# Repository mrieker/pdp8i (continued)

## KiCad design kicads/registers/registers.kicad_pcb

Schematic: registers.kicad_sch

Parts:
J1, J2, J3, J4: Conn_02x20_Odd_Even; PinHeader_2x20_P2.54mm_Vertical
U1, U10, U19, U51: 74HC86; DIP-14_W7.62mm
U2, U3, U4, U5, U11, U12, U17, U18, U20, U21, U22, U26, U27, U52, U53, U54, U55, U56: 74LS153; DIP-16_W7.62mm
U6, U14, U23: 74LS283; DIP-16_W7.62mm
U7, U15, U24, U58, U85, U91, U117: 74LS08; DIP-14_W7.62mm
U8, U16, U25, U77: 74LS32; DIP-14_W7.62mm
U9, U62, U72, U73, U76, U78, U79, U82, U105, U113: 74LS10; DIP-14_W7.62mm
U13, U59, U63, U65, U66, U69, U74, U86, U97: 74LS00; DIP-14_W7.62mm
U28, U29, U30, U31, U32, U33: 74LS174; DIP-16_W7.62mm
U34, U35, U36: 74LS161; DIP-16_W7.62mm
U37, U38, U39, U40, U41, U42, U43, U44, U45, U46, U47, U48, U49: 74LS151; DIP-16_W7.62mm
U50, U104, U119, U120: 74HC74; DIP-14_W7.62mm
U57, U67, U90: 74LS04; DIP-14_W7.62mm
U60: 74LS02; DIP-14_W7.62mm
U61, U68, U70, U87, U89, U96: 74LS20; DIP-14_W7.62mm
U64, U75, U83, U88, U99: 74LS30; DIP-14_W7.62mm
U71, U106, U107, U108: 74LS11; DIP-14_W7.62mm
U80, U81, U110, U116, U118: 74HC00; DIP-14_W7.62mm
U84: 74LS175; DIP-16_W7.62mm
U92: 74HC138; DIP-16_W7.62mm
U93, U102, U109, U115: 74HC04; DIP-14_W7.62mm
U94, U98, U101, U112: 74LS27; DIP-14_W7.62mm
U95: 74LS21; DIP-14_W7.62mm
U100: 74HC02; DIP-14_W7.62mm
U103, U114: 74LS42; DIP-16_W7.62mm
U111: 74HC4075; DIP-14_W7.62mm

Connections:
/AA: U81.6, U101.3, U112.9
/ACCLEAR: J4.7, U118.5
/ACUM_0: J3.15, U1.1, U28.2 (Q0), U94.11
/ACUM_1: J3.7, U1.4, U28.5 (Q1), U94.10
/ACUM_2: J2.35, U1.9, U28.7 (Q2), U94.9
/ACUM_3: J2.27, U1.12, U28.10 (Q3), U98.11
/ACUM_4: J2.19, U10.1, U28.12 (Q4), U98.10
/ACUM_5: J2.12, U10.4, U28.15 (Q5), U98.9
/ACUM_6: J2.5, U10.9, U29.2 (Q0), U98.5
/ACUM_7: J1.34, U10.12, U29.5 (Q1), U98.4
/ACUM_8: J1.27, U19.1, U29.7 (Q2), U98.3
/ACUM_9: J1.19, U19.4, U29.10 (Q3), U98.13
/ACUM_10: J1.11, U19.9, U29.12 (Q4), U98.2
/ACUM_11: J1.3, U19.12, U29.15 (Q5), U86.12, U98.1
/BB: U77.1, U87.8, U101.4
/BRKRQST: J4.8
/BRKWRM: J4.9, U66.2, U79.11
/BUSINI: J4.22
/BWCOV: J4.23, U62.13, U104.5 (Q)
/CAINC: J4.10, U63.13, U72.13
/CC: U76.8, U77.2
/CC3: U67.4, U111.1, U118.9
/CLOK2: J4.3, U119.3 (C), U119.11 (C)
/CYCLE3: J4.11, U90.3
/DD: U22.2 (S1), U52.2 (S1), U53.2 (S1), U54.2 (S1), U55.2 (S1), U56.2 (S1), U81.8, U101.9
/DMADR_0: J3.18, U53.4 (I2a)
/DMADR_1: J3.10, U53.12 (I2b)
/DMADR_2: J2.38, U54.4 (I2a)
/DMADR_3: J2.30, U54.12 (I2b)
/DMADR_4: J2.22, U55.4 (I2a)
/DMADR_5: J2.15, U55.12 (I2b)
/DMADR_6: J2.8, U56.4 (I2a)
/DMADR_7: J1.37, U56.12 (I2b)
/DMADR_8: J1.30, U22.4 (I2a)
/DMADR_9: J1.22, U22.12 (I2b)
/DMADR_10: J1.14, U52.4 (I2a)
/DMADR_11: J1.6, U52.12 (I2b)
/DMADR_12: J3.25
/DMADR_13: J3.24
/DMADR_14: J3.23
/EE: U101.10, U105.8
/EXEFET: J4.24
/FF: U60.5, U96.8, U100.6, U101.11
/FLDSEL_0: J4.37
/FLDSEL_1: J4.38
/HH: U57.12, U112.1, U112.3
/HOLD: J4.12
/INBUS_0: J3.19, U53.5 (I1a)
/INBUS_1: J3.11, U53.11 (I1b)
/INBUS_2: J3.3, U54.5 (I1a)
/INBUS_3: J2.31, U54.11 (I1b)
/INBUS_4: J2.23, U55.5 (I1a)
/INBUS_5: J2.17, U55.11 (I1b)
/INBUS_6: J2.9, U56.5 (I1a)
/INBUS_7: J1.38, U56.11 (I1b)
/INBUS_8: J1.31, U22.5 (I1a), U84.4 (D0)
/INBUS_9: J1.23, U22.11 (I1b), U84.5 (D1)
/INBUS_10: J1.15, U52.5 (I1a), U84.12 (D2)
/INBUS_11: J1.7, U52.11 (I1b), U67.13
/INTAK: J4.25
/INTINH: J4.13
/INTRQST: J4.14
/IOP: J4.26, U63.4, U66.13, U109.3
/IOSKIP: J4.15, U62.5, U63.5
/IREG_8: U84.2 (Q0)
/IREG_9: J1.26, U84.7 (Q1), U92.1 (A0)
/IREG_10: J1.18, U84.10 (Q2), U92.2 (A1)
/IREG_11: J1.10, U84.14 (~Q3), U92.3 (A2)
/JJ: U60.6, U75.8, U100.5, U112.2, U112.4
/KK: U67.10, U112.10
/LINK: J4.27, U50.5 (Q), U51.5, U97.1
/LL: U89.6, U112.13
/LNKTOG: J4.16
/MADR_0: J3.16, U2.6 (I0a), U30.2 (Q0)
/MADR_1: J3.8, U2.10 (I0b), U30.5 (Q1)
/MADR_2: J2.36, U4.6 (I0a), U30.7 (Q2)
/MADR_3: J2.28, U4.10 (I0b), U30.10 (Q3), U95.5
/MADR_4: J2.20, U11.6 (I0a), U30.12 (Q4), U60.12
/MADR_5: J2.13, U11.10 (I0b), U30.15 (Q5), U60.11
/MADR_6: J2.6, U12.6 (I0a), U31.2 (Q0), U94.5
/MADR_7: J1.35, U12.10 (I0b), U31.5 (Q1), U91.13, U94.4
/MADR_8: J1.28, U20.6 (I0a), U31.7 (Q2), U91.10, U94.3
/MADR_9: J1.20, U20.10 (I0b), U31.10 (Q3), U91.5, U94.13
/MADR_10: J1.12, U21.6 (I0a), U31.12 (Q4), U91.2, U94.2
/MADR_11: J1.4, U21.10 (I0b), U31.15 (Q5), U58.13, U94.1
/MAJST_0: J4.20, U103.15 (A0)
/MAJST_1: J4.19, U103.14 (A1)
/MAJST_2: J4.18, U103.13 (A2)
/MAJST_3: J4.17, U57.11, U85.13, U103.12 (A3)
/MBUF_0: J3.17, U2.5 (I1a), U32.2 (Q0), U53.6 (I0a), U96.5, U101.13, U110.10
/MBUF_1: J3.9, U2.11 (I1b), U32.5 (Q1), U53.10 (I0b), U69.5
/MBUF_2: J2.37, U4.5 (I1a), U32.7 (Q2), U54.6 (I0a), U69.10, U77.5
/MBUF_3: J2.29, U4.11 (I1b), U32.10 (Q3), U51.10, U54.10 (I0b), U69.13
/MBUF_4: J2.21, U11.5 (I1a), U32.12 (Q4), U55.6 (I0a), U71.5, U97.2
/MBUF_5: J2.14, U11.11 (I1b), U32.15 (Q5), U55.10 (I0b), U71.9, U99.12
/MBUF_6: J2.7, U12.5 (I1a), U33.2 (Q0), U56.6 (I0a), U70.5, U86.13
/MBUF_7: J1.36, U33.5 (Q1), U56.10 (I0b), U58.12, U68.5, U91.1, U91.4, U91.9, U91.12, U118.10
/MBUF_8: J1.29, U22.6 (I0a), U33.7 (Q2), U60.9, U67.9, U96.4, U100.3
/MBUF_9: J1.21, U22.10 (I0b), U33.10 (Q3)
/MBUF_10: J1.13, U33.12 (Q4), U52.6 (I0a)
/MBUF_11: J1.5, U33.15 (Q5), U52.10 (I0b)
/MM: U73.12, U112.5
/MQUO_0: J3.20
/MQUO_1: J3.12
/MQUO_2: J3.4
/MQUO_3: J2.32
/MQUO_4: J2.24
/MQUO_5: J2.16
/MQUO_6: J2.10
/MQUO_7: J2.3
/MQUO_8: J1.32
/MQUO_9: J1.24
/MQUO_10: J1.16
/MQUO_11: J1.8
/NN: U109.2, U110.9, U112.11
/NXTMSBRK: J4.21
/NXTMS_0: J3.30, U114.15 (A0)
/NXTMS_1: J3.29, U114.14 (A1)
/NXTMS_2: J3.28, U114.13 (A2)
/NXTMS_3: J3.27, U114.12 (A3)
/PCTR_0: J3.21, U2.4 (I2a), U34.14 (Q0)
/PCTR_1: J3.13, U2.12 (I2b), U34.13 (Q1)
/PCTR_2: J3.5, U4.4 (I2a), U34.12 (Q2)
/PCTR_3: J2.33, U4.12 (I2b), U34.11 (Q3)
/PCTR_4: J2.25, U11.4 (I2a), U35.14 (Q0)
/PCTR_5: J2.18, U11.12 (I2b), U35.13 (Q1)
/PCTR_6: J2.11, U12.4 (I2a), U35.12 (Q2)
/PCTR_7: J2.4, U12.12 (I2b), U35.11 (Q3)
/PCTR_8: J1.33, U20.4 (I2a), U36.14 (Q0)
/PCTR_9: J1.25, U20.12 (I2b), U36.13 (Q1)
/PCTR_10: J1.17, U21.4 (I2a), U36.12 (Q2)
/PCTR_11: J1.9, U21.12 (I2b), U36.11 (Q3)
/PP: U81.11
/READSR: J3.26, U111.9
/RESET: J4.4
/RUN: J4.28, U58.1
/SCTR_0: J3.22
/SCTR_1: J3.14
/SCTR_2: J3.6
/SCTR_3: J2.34
/SCTR_4: J2.26
/TP1: J4.33, U57.3, U85.1, U86.1
/TP2: J4.34, U13.4, U63.9, U68.1, U70.1, U117.4
/TP3: J4.35, U57.1, U58.4, U58.9
/TP4: J4.36, U116.4
/TS1: J4.29, U109.11
/TS2: J4.30, U13.12, U72.1, U73.3, U74.1, U78.1, U78.3, U79.1, U79.9, U80.9, U97.9, U117.10
/TS3: J4.31, U9.3, U13.1, U13.9, U66.12, U71.1, U71.3, U72.3, U72.9, U73.9, U74.9, U78.9, U79.3, U80.1, U82.1, U105.3
/TS4: J4.32, U70.9, U74.4, U74.12, U76.1, U76.3, U80.4, U80.12, U81.1, U86.9, U105.1
/_AA1: U81.4, U82.12
/_AA2: U81.5, U86.8
/_BB1: U87.9, U90.2
/_BB2: U87.10, U109.10
/_BB3: U79.8, U87.12
/_BB4: U74.3, U87.13
/_CC1: U66.11, U76.9, U118.12
/_CC2: U74.8, U76.10, U118.13
/_CC3: U9.6, U67.3, U76.11, U77.4
/_DD1: U74.6, U81.9
/_DD2: U76.12, U81.10
/_EE1: U72.6, U105.9
/_EE2: U76.6, U105.10
/_EE3: U74.11, U105.11
/_FF1: U78.12, U96.9
/_FF2: U78.6, U96.10
/_FF3: U96.12, U97.8
/_FF4: U72.12, U96.13
/_HH1: U57.13, U60.1
/_JJ1: U75.4, U86.6
/_JJ2: U75.5, U97.11
/_JJ3: U75.6, U79.6
/_JJ4: U75.11, U80.3
/_JJ5: U75.12, U80.6
/_KK1: U67.11, U73.6
/_LL1: U79.12, U89.1
/_LL2: U80.8, U89.2
/_LL3: U80.11, U89.4
/_LL4: U89.5, U105.12
/_MM1: U73.1, U78.8
/_MM2: U73.2, U81.3
/_MM3: U70.8, U73.13
/_NN1: U72.8, U109.1, U113.4
/_PP1: U73.8, U81.12, U109.5
/_PP2: U81.13, U105.6, U113.3
/_acres: U28.1 (~Mr), U29.1 (~Mr), U68.6
/_asel_0: U2.14 (S0), U4.14 (S0), U11.14 (S0), U12.14 (S0), U20.14 (S0), U21.14 (S0), U87.4, U112.12
/_asel_1: U2.2 (S1), U4.2 (S1), U11.2 (S1), U12.2 (S1), U20.2 (S1), U21.2 (S1), U87.5, U112.6
/_irand: U82.9, U92.15 (~Y0), U93.13
/_irdca: U82.11, U92.12 (~Y3), U93.5, U113.10
/_iriot: U92.9 (~Y6)
/_irisz: U92.13 (~Y2), U93.9, U113.9
/_irjmp: U60.8, U92.10 (~Y5), U93.1
/_irjms: U92.11 (~Y4), U93.3, U113.11
/_iropr: U67.5, U70.13, U92.7 (~Y7), U100.2, U101.1
/_irtad: U82.10, U92.14 (~Y1), U93.11
/_ldadclk: U9.1, U116.12, U119.8 (~Q)
/_lnres: U50.1 (~R), U70.6
/_msdepos: U64.12, U102.11, U103.10 (8)
/_msexec: U90.13, U103.4 (3), U116.1
/_msintak: U64.11, U89.13, U102.9, U103.9 (7)
/_mswrdct: U64.4, U102.1, U103.5 (4), U116.2
/_pcld: U34.9 (~PE), U35.9 (~PE), U36.9 (~PE), U58.3
/acclk: U28.9 (Cp), U29.9 (Cp), U58.8
/acxx_0: U1.3, U2.3 (I3a)
/acxx_1: U1.6, U2.13 (I3b)
/acxx_2: U1.8, U4.3 (I3a)
/acxx_3: U1.11, U4.13 (I3b)
/acxx_4: U10.3, U11.3 (I3a)
/acxx_5: U10.6, U11.13 (I3b)
/acxx_6: U10.8, U12.3 (I3a)
/acxx_7: U10.11, U12.13 (I3b)
/acxx_8: U19.3, U20.3 (I3a)
/acxx_9: U19.6, U20.13 (I3b)
/acxx_10: U19.8, U21.3 (I3a)
/acxx_11: U19.11, U21.13 (I3b)
/alua_0: U2.7 (Za), U6.5 (A1), U7.1, U8.1
/alua_1: U2.9 (Zb), U6.3 (A2), U7.4, U8.4
/alua_2: U4.7 (Za), U6.14 (A3), U7.9, U8.9
/alua_3: U4.9 (Zb), U6.12 (A4), U7.12, U8.12
/alua_4: U11.7 (Za), U14.5 (A1), U15.1, U16.1
/alua_5: U11.9 (Zb), U14.3 (A2), U15.4, U16.4
/alua_6: U12.7 (Za), U14.14 (A3), U15.9, U16.9
/alua_7: U12.9 (Zb), U14.12 (A4), U15.12, U16.12
/alua_8: U20.7 (Za), U23.5 (A1), U24.1, U25.1
/alua_9: U20.9 (Zb), U23.3 (A2), U24.4, U25.4
/alua_10: U21.7 (Za), U23.14 (A3), U24.9, U25.9
/alua_11: U21.9 (Zb), U23.12 (A4), U24.12, U25.12
/alub_0: U6.6 (B1), U7.2, U8.2, U53.7 (Za)
/alub_1: U6.2 (B2), U7.5, U8.5, U53.9 (Zb)
/alub_2: U6.15 (B3), U7.10, U8.10, U54.7 (Za)
/alub_3: U6.11 (B4), U7.13, U8.13, U54.9 (Zb)
/alub_4: U14.6 (B1), U15.2, U16.2, U55.7 (Za)
/alub_5: U14.2 (B2), U15.5, U16.5, U55.9 (Zb)
/alub_6: U14.15 (B3), U15.10, U16.10, U56.7 (Za)
/alub_7: U14.11 (B4), U15.13, U16.13, U56.9 (Zb)
/alub_8: U22.7 (Za), U23.6 (B1), U24.2, U25.2
/alub_9: U22.9 (Zb), U23.2 (B2), U24.5, U25.5
/alub_10: U23.15 (B3), U24.10, U25.10, U52.7 (Za)
/alub_11: U23.11 (B4), U24.13, U25.13, U52.9 (Zb)
/aluq_0: U3.7 (Za), U30.3 (D0), U32.3 (D0), U34.3 (D0), U37.12 (I7), U38.14 (I5), U39.15 (I4), U43.13 (I6), U48.2 (I2), U49.1 (I3)
/aluq_1: U3.9 (Zb), U30.4 (D1), U32.4 (D1), U34.4 (D1), U37.1 (I3), U38.12 (I7), U39.14 (I5), U40.15 (I4), U44.13 (I6), U49.2 (I2)
/aluq_2: U5.7 (Za), U30.6 (D2), U32.6 (D2), U34.5 (D2), U37.2 (I2), U38.1 (I3), U39.12 (I7), U40.14 (I5), U41.15 (I4), U45.13 (I6)
/aluq_3: U5.9 (Zb), U30.11 (D3), U32.11 (D3), U34.6 (D3), U38.2 (I2), U39.1 (I3), U40.12 (I7), U41.14 (I5), U42.15 (I4), U46.13 (I6)
/aluq_4: U17.7 (Za), U30.13 (D4), U32.13 (D4), U35.3 (D0), U39.2 (I2), U40.1 (I3), U41.12 (I7), U42.14 (I5), U43.15 (I4), U47.13 (I6)
/aluq_5: U17.9 (Zb), U30.14 (D5), U32.14 (D5), U35.4 (D1), U40.2 (I2), U41.1 (I3), U42.12 (I7), U43.14 (I5), U44.15 (I4), U48.13 (I6)
/aluq_6: U18.7 (Za), U31.3 (D0), U33.3 (D0), U35.5 (D2), U37.13 (I6), U41.2 (I2), U42.1 (I3), U43.12 (I7), U44.14 (I5), U45.15 (I4)
/aluq_7: U18.9 (Zb), U31.4 (D1), U33.4 (D1), U35.6 (D3), U38.13 (I6), U42.2 (I2), U43.1 (I3), U44.12 (I7), U45.14 (I5), U46.15 (I4)
/aluq_8: U26.7 (Za), U31.6 (D2), U33.6 (D2), U36.3 (D0), U39.13 (I6), U43.2 (I2), U44.1 (I3), U45.12 (I7), U46.14 (I5), U47.15 (I4)
/aluq_9: U26.9 (Zb), U31.11 (D3), U33.11 (D3), U36.4 (D1), U40.13 (I6), U44.2 (I2), U45.1 (I3), U46.12 (I7), U47.14 (I5), U48.15 (I4)
/aluq_10: U27.7 (Za), U31.13 (D4), U33.13 (D4), U36.5 (D2), U41.13 (I6), U45.2 (I2), U46.1 (I3), U47.12 (I7), U48.14 (I5), U49.15 (I4)
/aluq_11: U27.9 (Zb), U31.14 (D5), U33.14 (D5), U36.6 (D3), U37.15 (I4), U42.13 (I6), U46.2 (I2), U47.1 (I3), U48.12 (I7), U49.14 (I5)
/aluq_12: U37.14 (I5), U38.15 (I4), U47.2 (I2), U48.1 (I3), U49.12 (I7), U49.13 (I6), U51.3
/autoinc: U65.5, U78.13, U95.6
/azero: U2.1 (Ea), U2.15 (Eb), U4.1 (Ea), U4.15 (Eb), U11.1 (Ea), U11.15 (Eb), U12.1 (Ea), U12.15 (Eb), U20.1 (Ea), U20.15 (Eb), U21.1 (Ea), U21.15 (Eb), U110.3
/bsel_0: U22.14 (S0), U52.14 (S0), U53.14 (S0), U54.14 (S0), U55.14 (S0), U56.14 (S0), U77.3
/bzero: U22.1 (Ea), U22.15 (Eb), U52.1 (Ea), U52.15 (Eb), U53.1 (Ea), U53.15 (Eb), U54.1 (Ea), U54.15 (Eb), U55.1 (Ea), U55.15 (Eb), U56.1 (Ea), U56.15 (Eb), U87.6
/cclears: U101.5, U118.3
/cin: U6.7 (C0), U110.6
/comac: U1.2, U1.5, U1.10, U1.13, U10.2, U10.5, U10.10, U10.13, U19.2, U19.5, U19.10, U19.13, U71.8
/comln: U51.4, U71.6
/cout: U23.9 (C4), U51.1, U104.2 (D)
/dirjmp: U59.5, U60.10, U78.11
/efaddr_7: U12.11 (I1b), U91.11
/efaddr_8: U20.5 (I1a), U91.8
/efaddr_9: U20.11 (I1b), U91.6
/efaddr_10: U21.5 (I1a), U91.3
/efaddr_11: U21.11 (I1b), U58.11
/extarithexec: U74.10, U109.13, U110.11
/g2skip: U9.11, U51.8
/group1: U68.4, U70.4, U71.2, U71.4, U71.10, U72.11, U77.12, U100.1, U116.10
/group2: U9.5, U9.10, U77.13, U101.12
/irand: U73.11, U93.12
/irandtaddca: U66.10, U82.8
/irdca: U73.5, U82.13, U93.6
/irisz: U62.2, U78.5, U93.8
/irjmp: U59.2, U72.5, U93.2
/irjms: U59.10, U79.5, U79.13, U93.4
/iropr: U62.4, U67.6, U96.1, U97.4, U105.13
/irtad: U69.2, U93.10, U105.5
/lnclk: U50.3 (C), U58.6
/maload: U30.9 (Cp), U31.9 (Cp), U116.11
/mbload: U32.9 (Cp), U33.9 (Cp), U63.3
/msbreak: U66.1, U79.10, U102.6
/mscurad: U63.12, U72.2, U74.13, U102.4
/msdefer: U59.1, U65.4, U72.4, U76.5, U78.2, U90.10
/msdepos: U65.13, U74.2, U97.13, U102.10, U117.9
/msexam: U65.10, U86.5, U102.12
/msexec: U59.9, U62.1, U62.3, U65.1, U66.9, U69.1, U73.4, U73.10, U78.4, U79.2, U79.4, U82.2, U90.12, U97.5, U105.4
/msfetch: U9.4, U9.9, U13.5, U13.13, U59.4, U66.4, U68.2, U70.2, U70.12, U71.11, U71.13, U72.10, U78.10, U85.2, U90.8, U96.2, U116.9
/msintak: U80.2, U80.10, U86.2, U102.8
/mspwron: U90.6
/mswrdct: U80.5, U97.10, U102.2
/nxtmsbreak: U76.2, U115.12
/nxtmsdefer: U81.2, U115.6
/nxtmsexec: U70.10, U76.4, U105.2, U115.8
/nxtmsfetch: U80.13, U115.4
/nxtmsintak: U86.10, U109.8
/nxtmspwron: U115.2
/nxtmswrdct: U74.5, U115.10
/pcclk: U9.12, U34.2 (CP), U35.2 (CP), U36.2 (CP)
/pcinc: U34.7 (CEP), U34.10 (CET), U35.7 (CEP), U36.7 (CEP), U59.11
/qsel_0: U3.14 (S0), U5.14 (S0), U17.14 (S0), U18.14 (S0), U26.14 (S0), U27.14 (S0), U109.6
/qsel_1: U3.2 (S1), U5.2 (S1), U17.2 (S1), U18.2 (S1), U26.2 (S1), U27.2 (S1), U113.6
/qsum_0: U3.4 (I2a), U6.4 (S1)
/qsum_1: U3.12 (I2b), U6.1 (S2)
/qsum_2: U5.4 (I2a), U6.13 (S3)
/qsum_3: U5.12 (I2b), U6.10 (S4)
/rotq_0: U28.3 (D0), U37.5 (Z)
/rotq_1: U28.4 (D1), U38.5 (Z)
/rotq_2: U28.6 (D2), U39.5 (Z)
/rotq_3: U28.11 (D3), U40.5 (Z)
/rotq_4: U28.13 (D4), U41.5 (Z)
/rotq_5: U28.14 (D5), U42.5 (Z)
/rotq_6: U29.3 (D0), U43.5 (Z)
/rotq_7: U29.4 (D1), U44.5 (Z)
/rotq_8: U29.6 (D2), U45.5 (Z)
/rotq_9: U29.11 (D3), U46.5 (Z)
/rotq_10: U29.13 (D4), U47.5 (Z)
/rotq_11: U29.14 (D5), U48.5 (Z)
/rotq_12: U49.5 (Z), U50.2 (D)
/swCONT: J3.35, U85.12
/swDEPOS: J3.34, U65.12, U97.12
/swEXAM: J3.33, U65.9, U86.4
/swLDAD: J3.32, U57.9, U90.1, U111.2
/swSINST: J3.38
/swSSTEP: J3.37
/swSTART: J3.36, U60.2
/swSTOP: J3.31
GND: J1.39, J1.40, J2.39, J2.40, J3.39, J3.40, J4.39, J4.40, U2.8 (GND), U3.1 (Ea), U3.3 (I3a), U3.8 (GND), U3.13 (I3b), U3.15 (Eb), U4.8 (GND), U5.1 (Ea), U5.3 (I3a), U5.8 (GND), U5.13 (I3b), U5.15 (Eb), U6.8 (GND), U11.8 (GND), U12.8 (GND), U14.8 (GND), U17.1 (Ea), U17.3 (I3a), U17.8 (GND), U17.13 (I3b), U17.15 (Eb), U18.1 (Ea), U18.3 (I3a), U18.8 (GND), U18.13 (I3b), U18.15 (Eb), U20.8 (GND), U21.8 (GND), U22.8 (GND), U23.8 (GND), U26.1 (Ea), U26.3 (I3a), U26.8 (GND), U26.13 (I3b), U26.15 (Eb), U27.1 (Ea), U27.3 (I3a), U27.8 (GND), U27.13 (I3b), U27.15 (Eb), U28.8 (GND), U29.8 (GND), U30.8 (GND), U31.8 (GND), U32.8 (GND), U33.8 (GND), U34.8 (GND), U35.8 (GND), U36.8 (GND), U37.3 (I1), U37.4 (I0), U37.7 (~E), U37.8 (GND), U38.3 (I1), U38.4 (I0), U38.7 (~E), U38.8 (GND), U39.3 (I1), U39.4 (I0), U39.7 (~E), U39.8 (GND), U40.3 (I1), U40.4 (I0), U40.7 (~E), U40.8 (GND), U41.3 (I1), U41.4 (I0), U41.7 (~E), U41.8 (GND), U42.3 (I1), U42.4 (I0), U42.7 (~E), U42.8 (GND), U43.3 (I1), U43.4 (I0), U43.7 (~E), U43.8 (GND), U44.3 (I1), U44.4 (I0), U44.7 (~E), U44.8 (GND), U45.3 (I1), U45.4 (I0), U45.7 (~E), U45.8 (GND), U46.3 (I1), U46.4 (I0), U46.7 (~E), U46.8 (GND), U47.3 (I1), U47.4 (I0), U47.7 (~E), U47.8 (GND), U48.3 (I1), U48.4 (I0), U48.7 (~E), U48.8 (GND), U49.3 (I1), U49.4 (I0), U49.7 (~E), U49.8 (GND), U52.8 (GND), U53.8 (GND), U54.8 (GND), U55.8 (GND), U56.8 (GND), U84.8 (GND), U92.4 (~E0), U92.5 (~E1), U92.8 (GND), U103.8 (GND), U114.8 (GND)
unnamed: U3.6 (I0a), U8.3
unnamed: U3.10 (I0b), U8.6
unnamed: U3.5 (I1a), U7.3
unnamed: U3.11 (I1b), U7.6
unnamed: U5.6 (I0a), U8.8
unnamed: U5.10 (I0b), U8.11
unnamed: U5.5 (I1a), U7.8
unnamed: U5.11 (I1b), U7.11
unnamed: U13.2, U61.6
unnamed: U13.3, U59.13
unnamed: U9.2, U13.6
unnamed: U13.8, U58.2
unnamed: U13.10, U89.8
unnamed: U13.11, U59.12
unnamed: U6.9 (C4), U14.7 (C0)
unnamed: U14.9 (C4), U23.7 (C0)
unnamed: U14.4 (S1), U17.4 (I2a)
unnamed: U14.1 (S2), U17.12 (I2b)
unnamed: U14.13 (S3), U18.4 (I2a)
unnamed: U14.10 (S4), U18.12 (I2b)
unnamed: U16.3, U17.6 (I0a)
unnamed: U16.6, U17.10 (I0b)
unnamed: U15.3, U17.5 (I1a)
unnamed: U15.6, U17.11 (I1b)
unnamed: U16.8, U18.6 (I0a)
unnamed: U16.11, U18.10 (I0b)
unnamed: U15.8, U18.5 (I1a)
unnamed: U15.11, U18.11 (I1b)
unnamed: U23.4 (S1), U26.4 (I2a)
unnamed: U23.1 (S2), U26.12 (I2b)
unnamed: U23.13 (S3), U27.4 (I2a)
unnamed: U23.10 (S4), U27.12 (I2b)
unnamed: U25.3, U26.6 (I0a)
unnamed: U25.6, U26.10 (I0b)
unnamed: U24.3, U26.5 (I1a)
unnamed: U24.6, U26.11 (I1b)
unnamed: U25.8, U27.6 (I0a)
unnamed: U25.11, U27.10 (I0b)
unnamed: U24.8, U27.5 (I1a)
unnamed: U24.11, U27.11 (I1b)
unnamed: U34.15 (TC), U35.10 (CET)
unnamed: U35.15 (TC), U36.10 (CET)
unnamed: U37.11 (S0), U38.11 (S0), U39.11 (S0), U40.11 (S0), U41.11 (S0), U42.11 (S0), U43.11 (S0), U44.11 (S0), U45.11 (S0), U46.11 (S0), U47.11 (S0), U48.11 (S0), U49.11 (S0), U69.6
unnamed: U37.10 (S1), U38.10 (S1), U39.10 (S1), U40.10 (S1), U41.10 (S1), U42.10 (S1), U43.10 (S1), U44.10 (S1), U45.10 (S1), U46.10 (S1), U47.10 (S1), U48.10 (S1), U49.10 (S1), U69.8
unnamed: U37.9 (S2), U38.9 (S2), U39.9 (S2), U40.9 (S2), U41.9 (S2), U42.9 (S2), U43.9 (S2), U44.9 (S2), U45.9 (S2), U46.9 (S2), U47.9 (S2), U48.9 (S2), U49.9 (S2), U69.11
unnamed: U51.2, U51.6
unnamed: U51.9, U82.6
unnamed: U9.13, U57.2
unnamed: U57.4, U63.1
unnamed: U58.5, U62.8
unnamed: U58.10, U68.8
unnamed: U59.3, U89.10
unnamed: U59.6, U89.9
unnamed: U59.8, U89.12
unnamed: U60.3, U85.11
unnamed: U60.13, U95.4
unnamed: U9.8, U61.1
unnamed: U61.2, U62.12
unnamed: U61.4, U62.6
unnamed: U61.5, U63.6
unnamed: U62.11, U69.3
unnamed: U63.2, U63.8
unnamed: U63.10, U64.8
unnamed: U63.11, U64.5
unnamed: U64.2, U65.6
unnamed: U64.3, U65.3
unnamed: U64.6, U66.3
unnamed: U66.5, U77.11
unnamed: U66.6, U68.12
unnamed: U66.8, U68.10
unnamed: U69.4, U69.9, U69.12, U71.12
unnamed: U76.13, U90.4
unnamed: U77.6, U87.1
unnamed: U82.3, U86.11
unnamed: U82.4, U99.8
unnamed: U82.5, U97.3
unnamed: U84.9 (Cp), U85.3
unnamed: U67.12, U84.13 (D3)
unnamed: U84.1 (~Mr), U86.3
unnamed: U94.6, U95.2
unnamed: U94.8, U99.11
unnamed: U94.12, U95.1
unnamed: U98.6, U99.4, U99.5
unnamed: U98.8, U99.6
unnamed: U98.12, U99.1, U99.2, U99.3
unnamed: U100.4, U113.5
unnamed: U67.8, U101.2
unnamed: U101.6, U110.1
unnamed: U101.8, U110.2
unnamed: U90.5, U103.1 (0)
unnamed: U90.9, U103.2 (1)
unnamed: U90.11, U103.3 (2)
unnamed: U102.3, U103.6 (5)
unnamed: U102.5, U103.7 (6)
unnamed: U102.13, U103.11 (9)
unnamed: U104.3 (C), U117.6
unnamed: U68.9, U109.4
unnamed: U62.9, U68.13, U109.12
unnamed: U60.4, U110.4
unnamed: U110.5, U110.8
unnamed: U96.6, U110.12
unnamed: U97.6, U110.13
unnamed: U111.8, U117.8
unnamed: U87.2, U112.8
unnamed: U57.8, U113.1
unnamed: U65.8, U113.2
unnamed: U65.2, U113.8
unnamed: U65.11, U113.13
unnamed: U114.1 (0), U115.1
unnamed: U114.2 (1), U115.3
unnamed: U114.3 (2), U115.5
unnamed: U114.4 (3), U115.9
unnamed: U114.5 (4), U115.11
unnamed: U114.7 (6), U115.13
unnamed: U109.9, U114.9 (7)
unnamed: U116.3, U117.5
unnamed: U57.10, U116.5
unnamed: U62.10, U116.8
unnamed: U116.6, U116.13
unnamed: U118.1, U118.6
unnamed: U118.2, U118.8
unnamed: U118.4, U118.11
unnamed: U119.5 (Q), U119.12 (D)
unnamed: U113.12, U119.1 (~R), U119.13 (~R)
VCC: J1.1, J1.2, J2.1, J2.2, J3.1, J3.2, J4.1, J4.2, U2.16 (VCC), U3.16 (VCC), U4.16 (VCC), U5.16 (VCC), U6.16 (VCC), U11.16 (VCC), U12.16 (VCC), U14.16 (VCC), U17.16 (VCC), U18.16 (VCC), U20.16 (VCC), U21.16 (VCC), U22.16 (VCC), U23.16 (VCC), U26.16 (VCC), U27.16 (VCC), U28.16 (VCC), U29.16 (VCC), U30.1 (~Mr), U30.16 (VCC), U31.1 (~Mr), U31.16 (VCC), U32.1 (~Mr), U32.16 (VCC), U33.1 (~Mr), U33.16 (VCC), U34.1 (~MR), U34.16 (VCC), U35.1 (~MR), U35.16 (VCC), U36.1 (~MR), U36.16 (VCC), U37.16 (VCC), U38.16 (VCC), U39.16 (VCC), U40.16 (VCC), U41.16 (VCC), U42.16 (VCC), U43.16 (VCC), U44.16 (VCC), U45.16 (VCC), U46.16 (VCC), U47.16 (VCC), U48.16 (VCC), U49.16 (VCC), U50.4 (~S), U52.16 (VCC), U53.16 (VCC), U54.16 (VCC), U55.16 (VCC), U56.16 (VCC), U64.1, U75.1, U75.2, U75.3, U84.16 (VCC), U92.6 (E2), U92.16 (VCC), U103.16 (VCC), U104.1 (~R), U104.4 (~S), U114.16 (VCC), U119.2 (D), U119.4 (~S), U119.10 (~S)

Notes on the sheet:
TS3: MADR <= MADR + 1
TS4: MADR <= MBUF
TS2: MBUF <= MBUF + 1
TS2: MBUF <= PCTR
load MADR after a 2 cycle delay after LDAD,EXAM,DEPOS
TS3: ACUM <= ACUM + MBUF_0
clock in new MADR except EXAM and DEPOS cycles
swLDAD: MADR <= INBUS (swREG)
TS4: MADR <= efaddr
TS3: ACUM <= ACUM | INBUS (group2)
TS3: ACUM <= 0
TS4: MADR <= 0
LSB
AA: ? <= 0 : A=ZERO, B=ZERO, OR BB: ? <= INBUS : A=ZERO, B=INBUS, OR CC: ? <= ACUM | INBUS : A=ACUM, B=INBUS, OR DD: ? <= DMADR : A=ZERO, B=DMADR, OR EE: ? <= MBUF : A=ZERO, B=MBUF, OR FF: ? <= MBUF + 1 : A=ZERO, B=MBUF, ADD, CIN=1 HH: ? <= MADR : A=MADR, B=ZERO, OR JJ: ? <= MADR + 1 : A=MADR, B=ZE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
TS2: MBUF <= ACUM
contx | swSTART: PCTR <= MADR
INBUS ----- TS1: data from memory TS2 & BREAK & BRKWRM: dma data from i/o dev IOP: pio data from i/o device
TS3: ACUM <= ACUM + MBUF
TS3: PCTR <= efaddr
TS3: PCTR <= MADR + 1
AZERO = AA | BB | CC1 & ACCLR | CC2 & ACCLR | CC3 & G2CLA | DD | EE | FF ASEL_0 (PCTR,MADR) = HH | JJ | LL ASEL_1 (efad,MADR) = HH | JJ | MM BZERO = AA | CC3 & ~G2OSR | HH | JJ | KK | LL | MM | NN BSEL_0 (INBUS) = BB | CC BSEL_1 (DMADR) = DD CIN = FF | JJ | NN & MBUF_0 QSEL_0 (AND) = PP1 QSEL_1 (AD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
TS2: MBUF <= INBUS (swREG)
asserted (low) when doing Group2 CLA
MSB
TS4: MADR <= PCTR
TS4: MADR <= DMADR
gate SWREG onto INBUS * during TS3 of Group2 for OSR * while LDAD held down to load MADR * during TS2 while doing deposit
complement ACUM value * must have Group1 instr * must have CMA bit * must be doing FETCH cycle
Clear ACUM for Group1 CLA at TP2
TS2: MBUF <= INBUS (dma data)
TS3: ACUM <= ACUM | INBUS (io data)
asserted (high) to force zero in alua during TS3
TS1: MBUF <= INBUS (mem data)
swEXAM: MADR <= MADR + 1
save overflow bit at TP2 * EXEC: used for ISZ skip must be valid until same TP3 * WRDCT: used for BWCOV must be valid until BREAK TP3
swDEPOS: MADR <= MADR + 1
current cycle is performing extended arithmetic accumulator and link get clocked at TP3 in these cycles FETCH: must have opcode 111 1xx xxx xx1 EXEC: must have opcode 111 xxx xxx xxx it is only OPR opcode that uses EXEC state
low when doing Group2 with OSR bit low blocking SR coming in on INBUS
asserted (low) when ACCLEAR is asserted (high) and doing IOT or ext arith
TS3: ACUM <= ACUM | INBUS (ext arith)

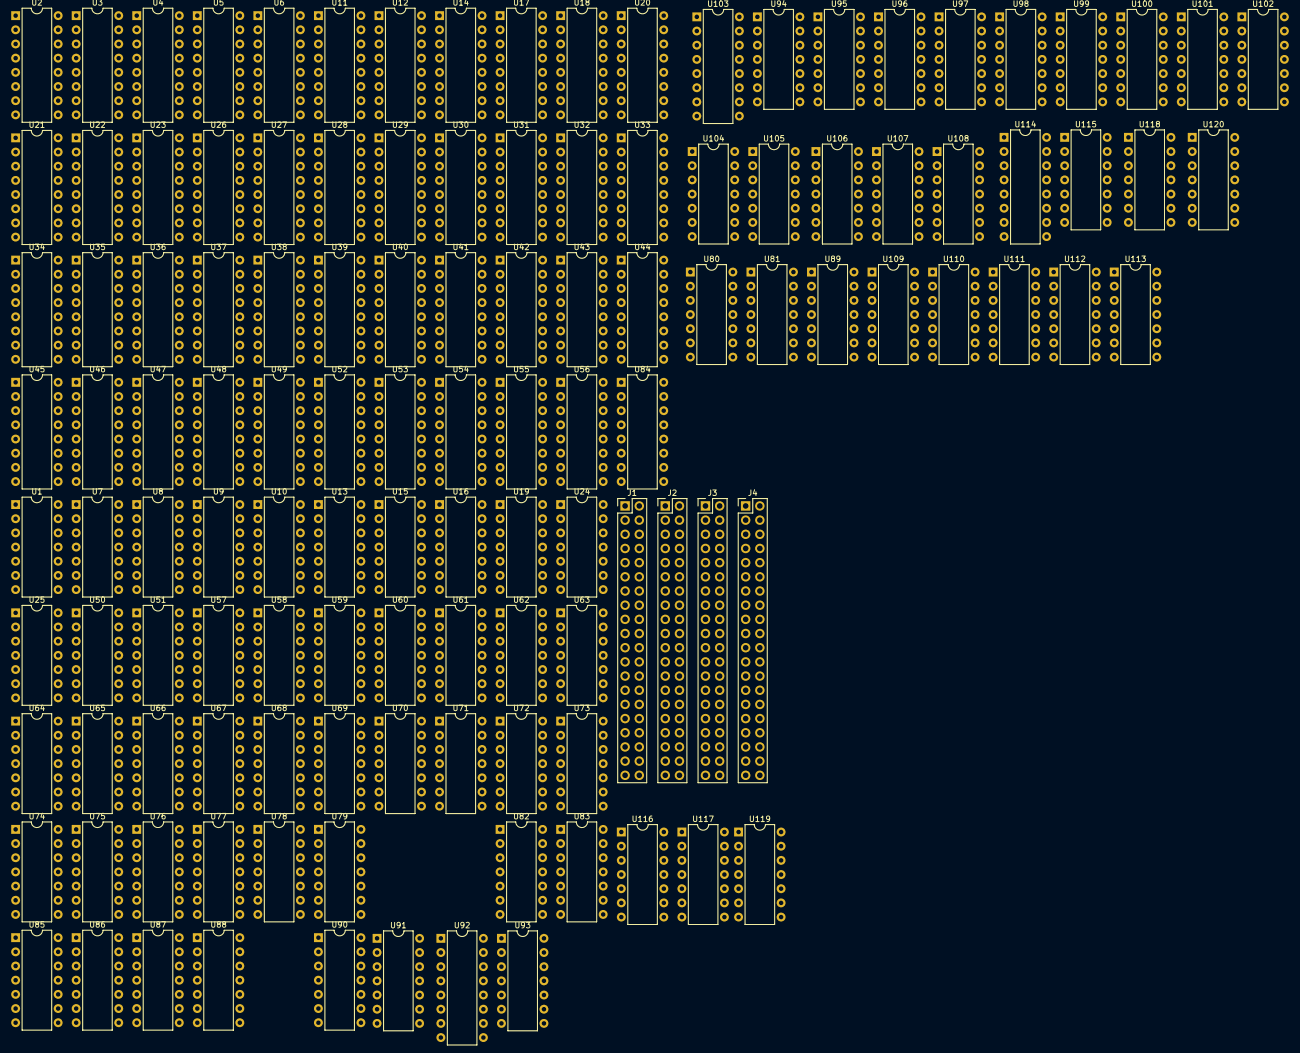
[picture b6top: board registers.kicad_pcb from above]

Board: 2 copper layers, 124 parts (0 on the bottom side), 414 nets, no tracks yet.

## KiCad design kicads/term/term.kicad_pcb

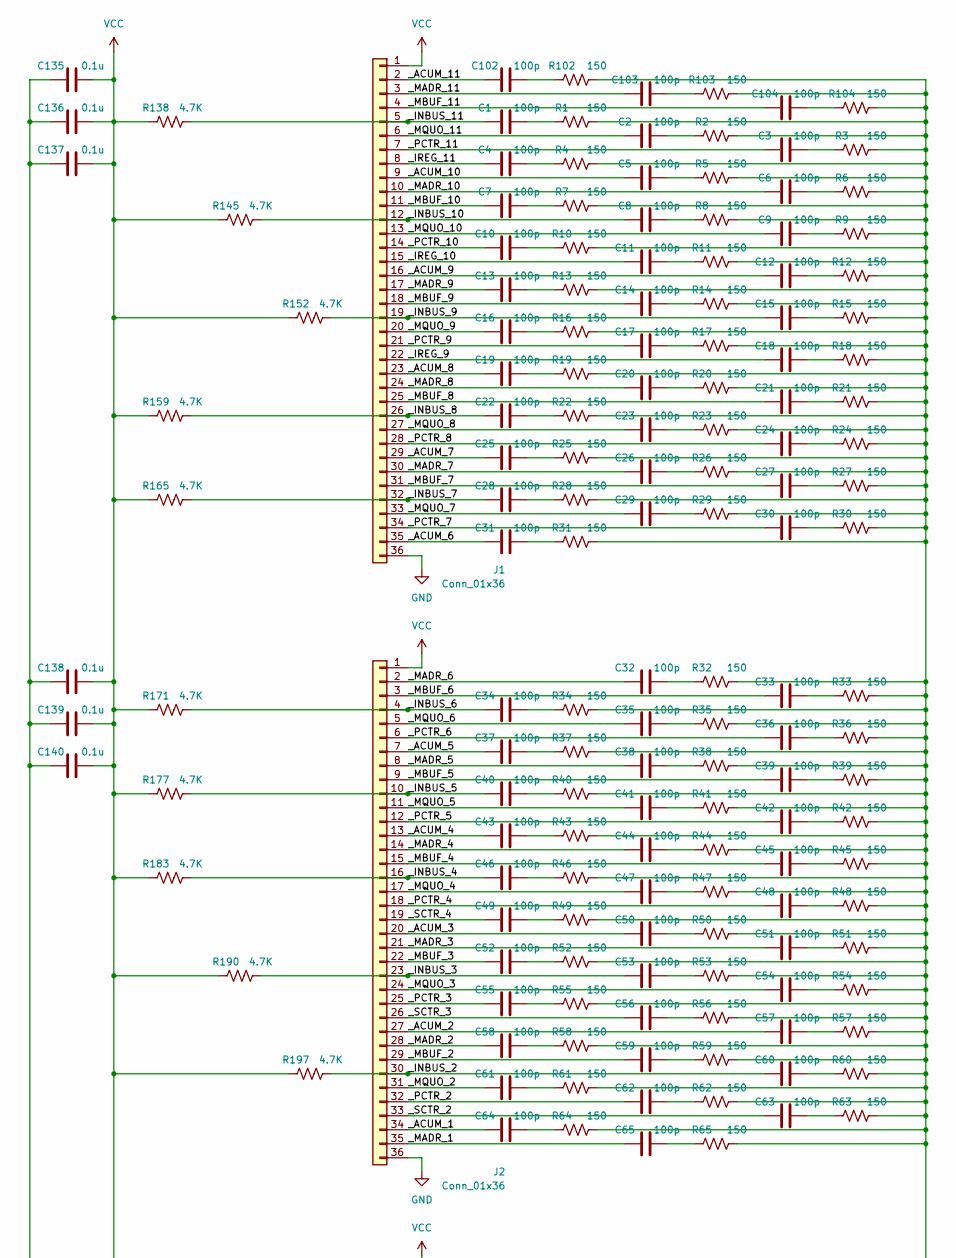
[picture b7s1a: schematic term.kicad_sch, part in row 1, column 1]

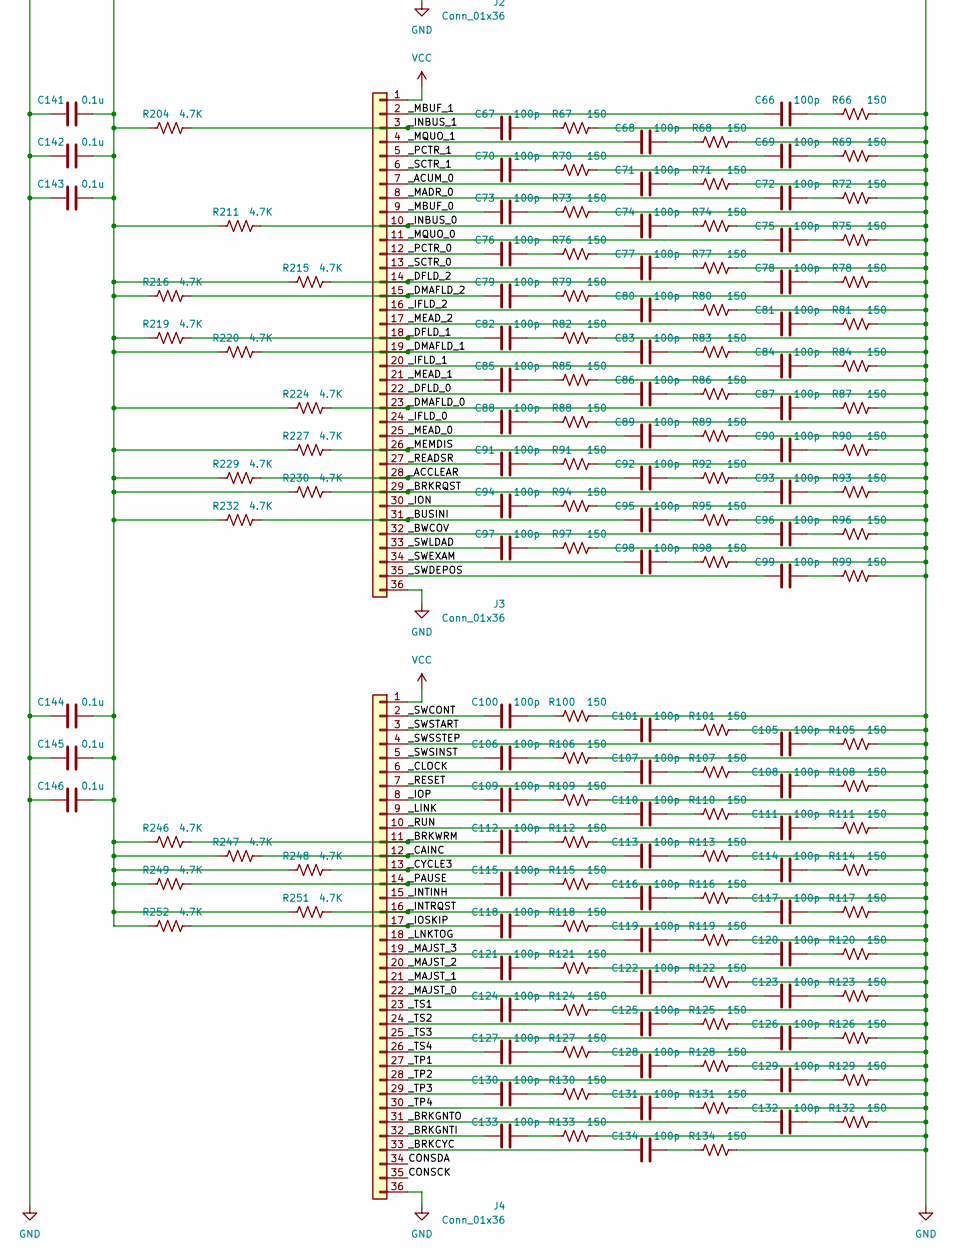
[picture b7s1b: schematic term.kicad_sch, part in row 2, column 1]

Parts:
C1, C2, C3, C4, C5, C6, C7, C8, C9, C10, C11, C12, C13, C14, C15, C16, C17, C18, C19, C20, C21, C22, C23, C24, C25, C26, C27, C28, C29, C30, C31, C32, C33, C34, C35, C36, C37, C38, C39, C40, C41, C42, C43, C44, C45, C46, C47, C48, C49, C50, C51, C52, C53, C54, C55, C56, C57, C58, C59, C60, C61, C62, C63, C64, C65, C66, C67, C68, C69, C70, C71, C72, C73, C74, C75, C76, C77, C78, C79, C80, C81, C82, C83, C84, C85, C86, C87, C88, C89, C90, C91, C92, C93, C94, C95, C96, C97, C98, C99, C100, C101, C102, C103, C104, C105, C106, C107, C108, C109, C110, C111, C112, C113, C114, C115, C116, C117, C118, C119, C120, C121, C122, C123, C124, C125, C126, C127, C128, C129, C130, C131, C132, C133, C134: 100p; R_Axial_DIN0207_L6.3mm_D2.5mm_P7.62mm_Horizontal
C135, C136, C137, C138, C139, C140, C141, C142, C143, C144, C145, C146: 0.1u; R_Axial_DIN0207_L6.3mm_D2.5mm_P7.62mm_Horizontal
J1, J2, J3, J4: Conn_01x36; PinHeader_1x36_P2.54mm_Vertical
R1, R2, R3, R4, R5, R6, R7, R8, R9, R10, R11, R12, R13, R14, R15, R16, R17, R18, R19, R20, R21, R22, R23, R24, R25, R26, R27, R28, R29, R30, R31, R32, R33, R34, R35, R36, R37, R38, R39, R40, R41, R42, R43, R44, R45, R46, R47, R48, R49, R50, R51, R52, R53, R54, R55, R56, R57, R58, R59, R60, R61, R62, R63, R64, R65, R66, R67, R68, R69, R70, R71, R72, R73, R74, R75, R76, R77, R78, R79, R80, R81, R82, R83, R84, R85, R86, R87, R88, R89, R90, R91, R92, R93, R94, R95, R96, R97, R98, R99, R100, R101, R102, R103, R104, R105, R106, R107, R108, R109, R110, R111, R112, R113, R114, R115, R116, R117, R118, R119, R120, R121, R122, R123, R124, R125, R126, R127, R128, R129, R130, R131, R132, R133, R134: 150; R_Axial_DIN0207_L6.3mm_D2.5mm_P7.62mm_Horizontal
R138, R145, R152, R159, R165, R171, R177, R183, R190, R197, R204, R211, R215, R216, R219, R220, R224, R227, R229, R230, R232, R246, R247, R248, R249, R251, R252: 4.7K; R_Axial_DIN0207_L6.3mm_D2.5mm_P7.62mm_Horizontal

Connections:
/CONSCK: J4.35
/CONSDA: J4.34
/_ACCLEAR: C92.1, J3.28, R229.2
/_ACUM_0: C71.1, J3.7
/_ACUM_1: C64.1, J2.34
/_ACUM_2: C57.1, J2.27
/_ACUM_3: C50.1, J2.20
/_ACUM_4: C43.1, J2.13
/_ACUM_5: C37.1, J2.7
/_ACUM_6: C31.1, J1.35
/_ACUM_7: C25.1, J1.29
/_ACUM_8: C19.1, J1.23
/_ACUM_9: C12.1, J1.16
/_ACUM_10: C5.1, J1.9
/_ACUM_11: C102.1, J1.2
/_BRKCYC: C134.1, J4.33
/_BRKGNTI: C133.1, J4.32
/_BRKGNTO: C132.1, J4.31
/_BRKRQST: C93.1, J3.29, R230.2
/_BRKWRM: C112.1, J4.11, R246.2
/_BUSINI: C95.1, J3.31, R232.2
/_BWCOV: C96.1, J3.32
/_CAINC: C113.1, J4.12, R247.2
/_CLOCK: C107.1, J4.6
/_CYCLE3: C114.1, J4.13, R248.2
/_DFLD_0: C86.1, J3.22
/_DFLD_1: C82.1, J3.18, R219.2
/_DFLD_2: C78.1, J3.14, R215.2
/_DMAFLD_0: C87.1, J3.23, R224.2
/_DMAFLD_1: C83.1, J3.19, R220.2
/_DMAFLD_2: C79.1, J3.15, R216.2
/_IFLD_0: C88.1, J3.24
/_IFLD_1: C84.1, J3.20
/_IFLD_2: C80.1, J3.16
/_INBUS_0: C74.1, J3.10, R211.2
/_INBUS_1: C67.1, J3.3, R204.2
/_INBUS_2: C60.1, J2.30, R197.2
/_INBUS_3: C53.1, J2.23, R190.2
/_INBUS_4: C46.1, J2.16, R183.2
/_INBUS_5: C40.1, J2.10, R177.2
/_INBUS_6: C34.1, J2.4, R171.2
/_INBUS_7: C28.1, J1.32, R165.2
/_INBUS_8: C22.1, J1.26, R159.2
/_INBUS_9: C15.1, J1.19, R152.2
/_INBUS_10: C8.1, J1.12, R145.2
/_INBUS_11: C1.1, J1.5, R138.2
/_INTINH: C116.1, J4.15
/_INTRQST: C117.1, J4.16, R251.2
/_ION: C94.1, J3.30
/_IOP: C109.1, J4.8
/_IOSKIP: C118.1, J4.17, R252.2
/_IREG_9: C18.1, J1.22
/_IREG_10: C11.1, J1.15
/_IREG_11: C4.1, J1.8
/_LINK: C110.1, J4.9
/_LNKTOG: C119.1, J4.18
/_MADR_0: C72.1, J3.8
/_MADR_1: C65.1, J2.35
/_MADR_2: C58.1, J2.28
/_MADR_3: C51.1, J2.21
/_MADR_4: C44.1, J2.14
/_MADR_5: C38.1, J2.8
/_MADR_6: C32.1, J2.2
/_MADR_7: C26.1, J1.30
/_MADR_8: C20.1, J1.24
/_MADR_9: C13.1, J1.17
/_MADR_10: C6.1, J1.10
/_MADR_11: C103.1, J1.3
/_MAJST_0: C123.1, J4.22
/_MAJST_1: C122.1, J4.21
/_MAJST_2: C121.1, J4.20
/_MAJST_3: C120.1, J4.19
/_MBUF_0: C73.1, J3.9
/_MBUF_1: C66.1, J3.2
/_MBUF_2: C59.1, J2.29
/_MBUF_3: C52.1, J2.22
/_MBUF_4: C45.1, J2.15
/_MBUF_5: C39.1, J2.9
/_MBUF_6: C33.1, J2.3
/_MBUF_7: C27.1, J1.31
/_MBUF_8: C21.1, J1.25
/_MBUF_9: C14.1, J1.18
/_MBUF_10: C7.1, J1.11
/_MBUF_11: C104.1, J1.4
/_MEAD_0: C89.1, J3.25
/_MEAD_1: C85.1, J3.21
/_MEAD_2: C81.1, J3.17
/_MEMDIS: C90.1, J3.26, R227.2
/_MQUO_0: C75.1, J3.11
/_MQUO_1: C68.1, J3.4
/_MQUO_2: C61.1, J2.31
/_MQUO_3: C54.1, J2.24
/_MQUO_4: C47.1, J2.17
/_MQUO_5: C41.1, J2.11
/_MQUO_6: C35.1, J2.5
/_MQUO_7: C29.1, J1.33
/_MQUO_8: C23.1, J1.27
/_MQUO_9: C16.1, J1.20
/_MQUO_10: C9.1, J1.13
/_MQUO_11: C2.1, J1.6
/_PAUSE: C115.1, J4.14, R249.2
/_PCTR_0: C76.1, J3.12
/_PCTR_1: C69.1, J3.5
/_PCTR_2: C62.1, J2.32
/_PCTR_3: C55.1, J2.25
/_PCTR_4: C48.1, J2.18
/_PCTR_5: C42.1, J2.12
/_PCTR_6: C36.1, J2.6
/_PCTR_7: C30.1, J1.34
/_PCTR_8: C24.1, J1.28
/_PCTR_9: C17.1, J1.21
/_PCTR_10: C10.1, J1.14
/_PCTR_11: C3.1, J1.7
/_READSR: C91.1, J3.27
/_RESET: C108.1, J4.7
/_RUN: C111.1, J4.10
/_SCTR_0: C77.1, J3.13
/_SCTR_1: C70.1, J3.6
/_SCTR_2: C63.1, J2.33
/_SCTR_3: C56.1, J2.26
/_SCTR_4: C49.1, J2.19
/_SWCONT: C100.1, J4.2
/_SWDEPOS: C99.1, J3.35
/_SWEXAM: C98.1, J3.34
/_SWLDAD: C97.1, J3.33
/_SWSINST: C106.1, J4.5
/_SWSSTEP: C105.1, J4.4
/_SWSTART: C101.1, J4.3
/_TP1: C128.1, J4.27
/_TP2: C129.1, J4.28
/_TP3: C130.1, J4.29
/_TP4: C131.1, J4.30
/_TS1: C124.1, J4.23
/_TS2: C125.1, J4.24
/_TS3: C126.1, J4.25
/_TS4: C127.1, J4.26
GND: C135.1, C136.1, C137.1, C138.1, C139.1, C140.1, C141.1, C142.1, C143.1, C144.1, C145.1, C146.1, J1.36, J2.36, J3.36, J4.36, R1.2, R2.2, R3.2, R4.2, R5.2, R6.2, R7.2, R8.2, R9.2, R10.2, R11.2, R12.2, R13.2, R14.2, R15.2, R16.2, R17.2, R18.2, R19.2, R20.2, R21.2, R22.2, R23.2, R24.2, R25.2, R26.2, R27.2, R28.2, R29.2, R30.2, R31.2, R32.2, R33.2, R34.2, R35.2, R36.2, R37.2, R38.2, R39.2, R40.2, R41.2, R42.2, R43.2, R44.2, R45.2, R46.2, R47.2, R48.2, R49.2, R50.2, R51.2, R52.2, R53.2, R54.2, R55.2, R56.2, R57.2, R58.2, R59.2, R60.2, R61.2, R62.2, R63.2, R64.2, R65.2, R66.2, R67.2, R68.2, R69.2, R70.2, R71.2, R72.2, R73.2, R74.2, R75.2, R76.2, R77.2, R78.2, R79.2, R80.2, R81.2, R82.2, R83.2, R84.2, R85.2, R86.2, R87.2, R88.2, R89.2, R90.2, R91.2, R92.2, R93.2, R94.2, R95.2, R96.2, R97.2, R98.2, R99.2, R100.2, R101.2, R102.2, R103.2, R104.2, R105.2, R106.2, R107.2, R108.2, R109.2, R110.2, R111.2, R112.2, R113.2, R114.2, R115.2, R116.2, R117.2, R118.2, R119.2, R120.2, R121.2, R122.2, R123.2, R124.2, R125.2, R126.2, R127.2, R128.2, R129.2, R130.2, R131.2, R132.2, R133.2, R134.2
unnamed: C1.2, R1.1
unnamed: C2.2, R2.1
unnamed: C3.2, R3.1
unnamed: C4.2, R4.1
unnamed: C5.2, R5.1
unnamed: C6.2, R6.1
unnamed: C7.2, R7.1
unnamed: C8.2, R8.1
unnamed: C9.2, R9.1
unnamed: C10.2, R10.1
unnamed: C11.2, R11.1
unnamed: C12.2, R12.1
unnamed: C13.2, R13.1
unnamed: C14.2, R14.1
unnamed: C15.2, R15.1
unnamed: C16.2, R16.1
unnamed: C17.2, R17.1
unnamed: C18.2, R18.1
unnamed: C19.2, R19.1
unnamed: C20.2, R20.1
unnamed: C21.2, R21.1
unnamed: C22.2, R22.1
unnamed: C23.2, R23.1
unnamed: C24.2, R24.1
unnamed: C25.2, R25.1
unnamed: C26.2, R26.1
unnamed: C27.2, R27.1
unnamed: C28.2, R28.1
unnamed: C29.2, R29.1
unnamed: C30.2, R30.1
unnamed: C31.2, R31.1
unnamed: C32.2, R32.1
unnamed: C33.2, R33.1
unnamed: C34.2, R34.1
unnamed: C35.2, R35.1
unnamed: C36.2, R36.1
unnamed: C37.2, R37.1
unnamed: C38.2, R38.1
unnamed: C39.2, R39.1
unnamed: C40.2, R40.1
unnamed: C41.2, R41.1
unnamed: C42.2, R42.1
unnamed: C43.2, R43.1
unnamed: C44.2, R44.1
unnamed: C45.2, R45.1
unnamed: C46.2, R46.1
unnamed: C47.2, R47.1
unnamed: C48.2, R48.1
unnamed: C49.2, R49.1
unnamed: C50.2, R50.1
unnamed: C51.2, R51.1
unnamed: C52.2, R52.1
unnamed: C53.2, R53.1
unnamed: C54.2, R54.1
unnamed: C55.2, R55.1
unnamed: C56.2, R56.1
unnamed: C57.2, R57.1
unnamed: C58.2, R58.1
unnamed: C59.2, R59.1
unnamed: C60.2, R60.1
unnamed: C61.2, R61.1
unnamed: C62.2, R62.1
unnamed: C63.2, R63.1
unnamed: C64.2, R64.1
unnamed: C65.2, R65.1
unnamed: C66.2, R66.1
unnamed: C67.2, R67.1
unnamed: C68.2, R68.1
unnamed: C69.2, R69.1
unnamed: C70.2, R70.1
unnamed: C71.2, R71.1
unnamed: C72.2, R72.1
unnamed: C73.2, R73.1
unnamed: C74.2, R74.1
unnamed: C75.2, R75.1
unnamed: C76.2, R76.1
unnamed: C77.2, R77.1
unnamed: C78.2, R78.1
unnamed: C79.2, R79.1
unnamed: C80.2, R80.1
unnamed: C81.2, R81.1
unnamed: C82.2, R82.1
unnamed: C83.2, R83.1
unnamed: C84.2, R84.1
unnamed: C85.2, R85.1
unnamed: C86.2, R86.1
unnamed: C87.2, R87.1
unnamed: C88.2, R88.1
unnamed: C89.2, R89.1
unnamed: C90.2, R90.1
unnamed: C91.2, R91.1
unnamed: C92.2, R92.1
unnamed: C93.2, R93.1
unnamed: C94.2, R94.1
unnamed: C95.2, R95.1
unnamed: C96.2, R96.1
unnamed: C97.2, R97.1
unnamed: C98.2, R98.1
unnamed: C99.2, R99.1
unnamed: C100.2, R100.1
unnamed: C101.2, R101.1
unnamed: C102.2, R102.1
unnamed: C103.2, R103.1
unnamed: C104.2, R104.1
unnamed: C105.2, R105.1
unnamed: C106.2, R106.1
unnamed: C107.2, R107.1
unnamed: C108.2, R108.1
unnamed: C109.2, R109.1
unnamed: C110.2, R110.1
unnamed: C111.2, R111.1
unnamed: C112.2, R112.1
unnamed: C113.2, R113.1
unnamed: C114.2, R114.1
unnamed: C115.2, R115.1
unnamed: C116.2, R116.1
unnamed: C117.2, R117.1
unnamed: C118.2, R118.1
unnamed: C119.2, R119.1
unnamed: C120.2, R120.1
unnamed: C121.2, R121.1
unnamed: C122.2, R122.1
unnamed: C123.2, R123.1
unnamed: C124.2, R124.1
unnamed: C125.2, R125.1
unnamed: C126.2, R126.1
unnamed: C127.2, R127.1
unnamed: C128.2, R128.1
unnamed: C129.2, R129.1
unnamed: C130.2, R130.1
unnamed: C131.2, R131.1
unnamed: C132.2, R132.1
unnamed: C133.2, R133.1
unnamed: C134.2, R134.1
VCC: C135.2, C136.2, C137.2, C138.2, C139.2, C140.2, C141.2, C142.2, C143.2, C144.2, C145.2, C146.2, J1.1, J2.1, J3.1, J4.1, R138.1, R145.1, R152.1, R159.1, R165.1, R171.1, R177.1, R183.1, R190.1, R197.1, R204.1, R211.1, R215.1, R216.1, R219.1, R220.1, R224.1, R227.1, R229.1, R230.1, R232.1, R246.1, R247.1, R248.1, R249.1, R251.1, R252.1
